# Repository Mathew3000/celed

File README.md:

This is a Mirror of: [ceLED](https://git.hacksaar.de/Mathew3000/celed/ "base page")

# CeLED

A small PCB containing an esp32 microcontroller to controll WS2812B LEDs.
The board is designed to deliver up to 3A to the LEDs as long as your PSU can supply it.
While it's originally designed to be used with WLED, feel free to use what you whant.

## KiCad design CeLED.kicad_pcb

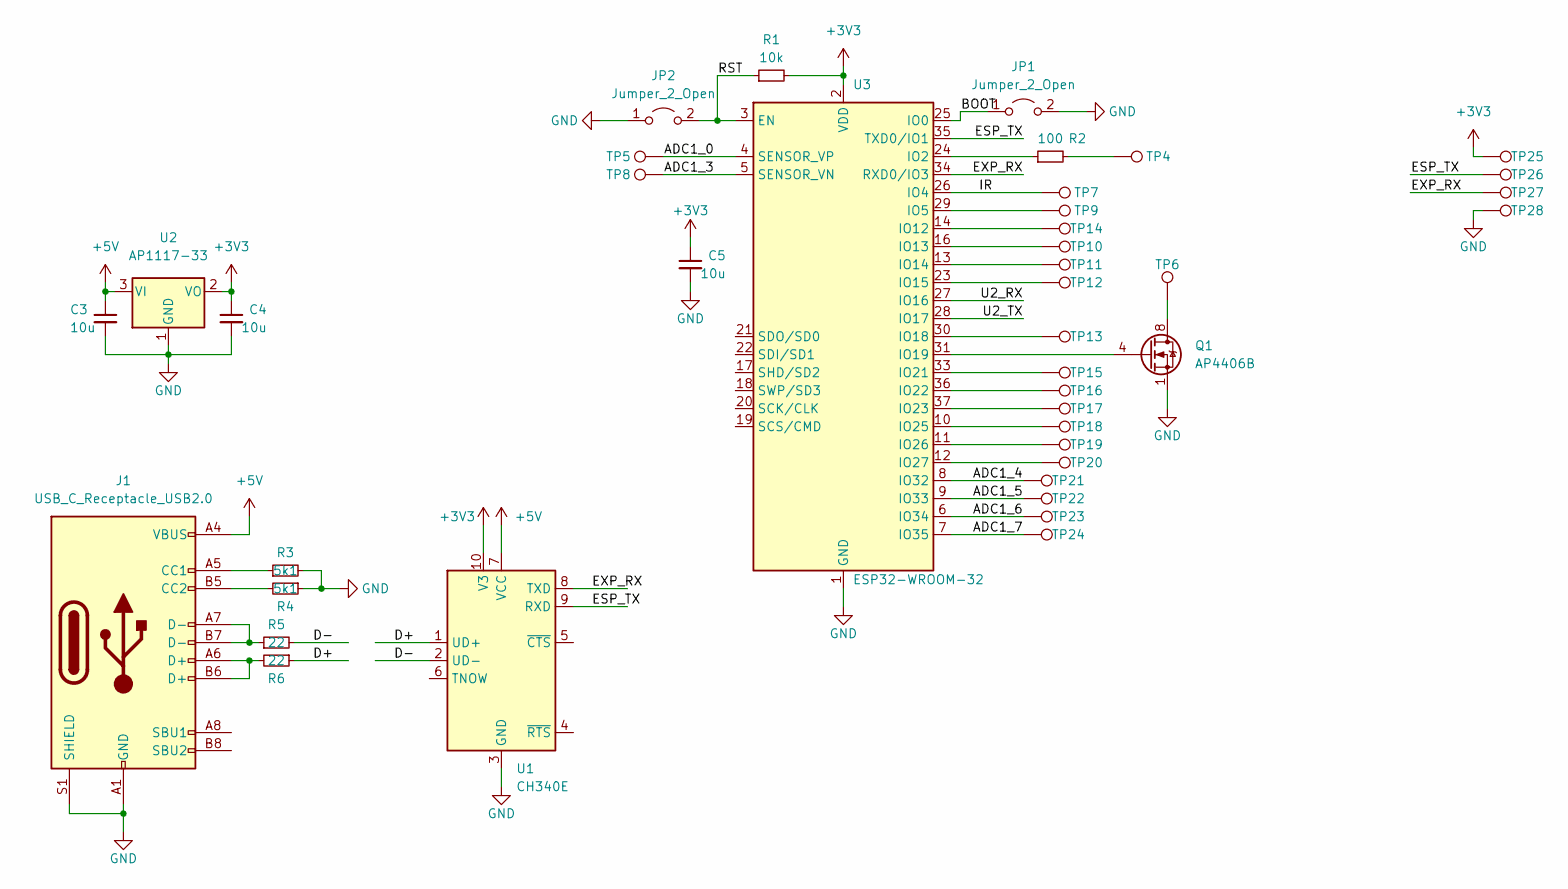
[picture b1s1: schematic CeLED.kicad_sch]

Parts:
C3, C4, C5: 10u; C_0805_2012Metric
J1: USB_C_Receptacle_USB2.0; USB_C_Receptacle_GCT_USB4085
JP1, JP2: Jumper_2_Open; SolderJumper-2_P1.3mm_Open_RoundedPad1.0x1.5mm
Q1: AP4406B; SOP-8_3.76x4.96mm_P1.27mm
R1: 10k; R_0603_1608Metric
R2: 100; R_0603_1608Metric
R3, R4: 5k1; R_0603_1608Metric
R5, R6: 22; R_0603_1608Metric
TP4, TP6: TestPoint; TestPoint_Pad_2.0x2.0mm
TP5, TP7, TP8, TP9, TP10, TP11, TP12, TP13, TP14, TP15, TP16, TP17, TP18, TP19, TP20, TP21, TP22, TP23, TP24: TestPoint; TestPoint_Pad_D1.5mm
TP25, TP26, TP27, TP28: TestPoint; TestPoint_Pad_D1.0mm
U1: CH340E; MSOP-10_3x3mm_P0.5mm
U2: AP1117-33; SOT-223-3_TabPin2
U3: ESP32-WROOM-32

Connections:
+3V3: C4.1, C5.1, R1.2, TP25.1, U1.10 (V3), U2.2 (VO), U3.2 (VDD)
+5V: C3.1, J1.A4 (VBUS), J1.A9 (VBUS), J1.B4 (VBUS), J1.B9 (VBUS), U1.7 (VCC), U2.3 (VI); also elsewhere on the board
/ADC1_0: TP5.1, U3.4 (SENSOR_VP)
/ADC1_3: TP8.1, U3.5 (SENSOR_VN)
/ADC1_4: TP21.1, U3.8 (IO32)
/ADC1_5: TP22.1, U3.9 (IO33)
/ADC1_6: TP23.1, U3.6 (IO34)
/ADC1_7: TP24.1, U3.7 (IO35)
/BOOT: JP1.1 (A), U3.25 (IO0)
/D+: R6.1, U1.1 (UD+)
/D-: R5.2, U1.2 (UD-)
/ESP_TX: TP26.1, U1.9 (RXD), U3.35 (TXD0/IO1)
/EXP_RX: TP27.1, U1.8 (TXD), U3.34 (RXD0/IO3)
/IR: TP7.1, U3.26 (IO4)
/RST: JP2.2 (B), R1.1, U3.3 (EN)
/U2_RX: U3.27 (IO16)
/U2_TX: U3.28 (IO17)
GND: C3.2, C4.2, C5.2, J1.A1 (GND), J1.A12 (GND), J1.B1 (GND), J1.B12 (GND), J1.S1 (SHIELD), JP1.2 (B), JP2.1 (A), Q1.1 (S), Q1.2 (S), Q1.3 (S), R3.2, R4.1, TP28.1, U1.3 (GND), U2.1 (GND), U3.1 (GND), U3.15 (GND), U3.38 (GND), U3.39 (GND)
unnamed: J1.A5 (CC1), R3.1
unnamed: J1.A6 (D+), J1.B6 (D+), R6.2
unnamed: J1.A7 (D-), J1.B7 (D-), R5.1
unnamed: J1.B5 (CC2), R4.2
unnamed: Q1.4 (G), U3.31 (IO19)
unnamed: Q1.5 (D), Q1.6 (D), Q1.7 (D), Q1.8 (D), TP6.1
unnamed: R2.1, U3.24 (IO2)
unnamed: R2.2, TP4.1
unnamed: TP9.1, U3.29 (IO5)
unnamed: TP10.1, U3.16 (IO13)
unnamed: TP11.1, U3.13 (IO14)
unnamed: TP12.1, U3.23 (IO15)
unnamed: TP13.1, U3.30 (IO18)
unnamed: TP14.1, U3.14 (IO12)
unnamed: TP15.1, U3.33 (IO21)
unnamed: TP16.1, U3.36 (IO22)
unnamed: TP17.1, U3.37 (IO23)
unnamed: TP18.1, U3.10 (IO25)
unnamed: TP19.1, U3.11 (IO26)
unnamed: TP20.1, U3.12 (IO27)

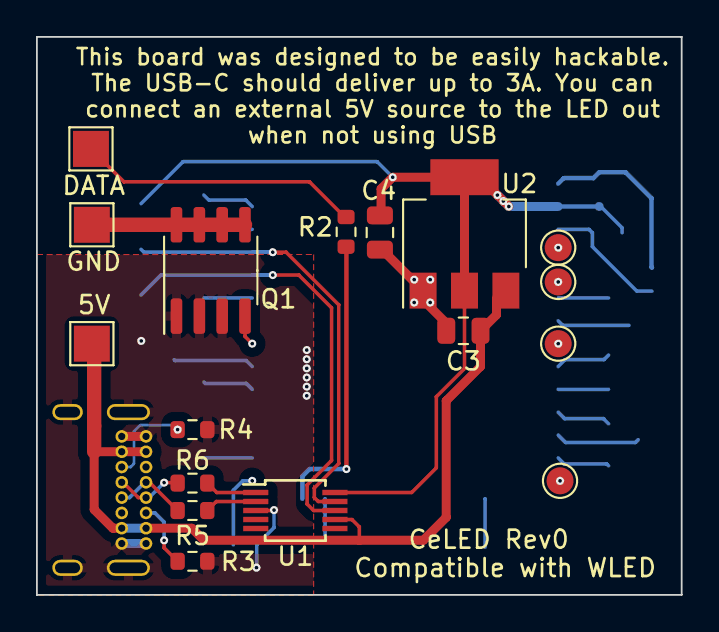
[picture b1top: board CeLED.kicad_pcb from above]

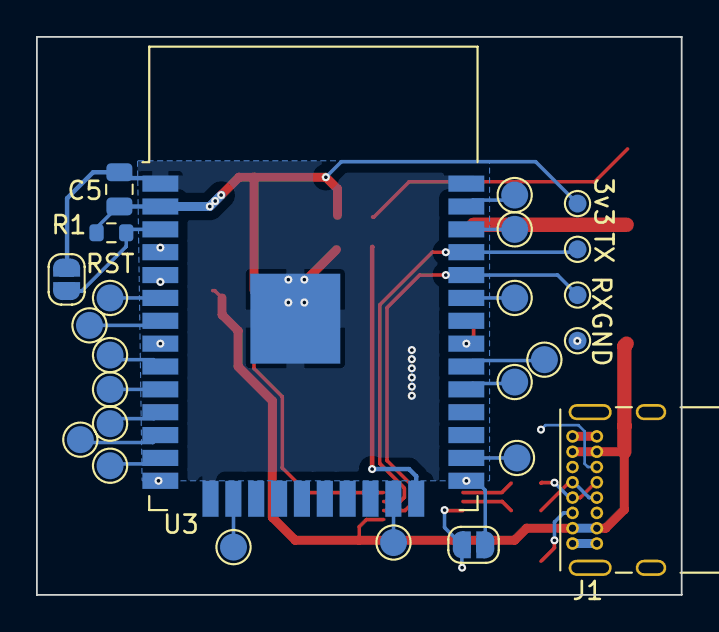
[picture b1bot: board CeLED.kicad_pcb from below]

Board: 2 copper layers, 35.8 x 31.0 mm, 42 parts (25 on the bottom side), 36 nets.

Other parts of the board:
TP2: TestPoint; TestPoint_Pad_2.0x2.0mm

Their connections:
+5V: TP2.1; also elsewhere on the board

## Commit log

2023-01-12 added gitignore
2023-01-12 initial upload
2023-01-12 added readme
